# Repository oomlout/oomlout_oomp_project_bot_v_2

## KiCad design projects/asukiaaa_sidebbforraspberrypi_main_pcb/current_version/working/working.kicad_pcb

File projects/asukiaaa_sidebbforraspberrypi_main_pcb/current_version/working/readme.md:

# sidebbforraspberrypi
 
## summary 
* id: asukiaaa_sidebbforraspberrypi_main_pcb
* user: asukiaaa
* name: sidebbforraspberrypi
* board: main_pcb
* repo: https://github.com/asukiaaa/SideBBForRaspberryPi
* src_file_repo_kicad_pcb: main_pcb/main_pcb.kicad_pcb
* src_file_repo_kicad_pcb_link: https://github.com/asukiaaa/SideBBForRaspberryPi/tree/master/main_pcb/main_pcb.kicad_pcb

* src_file_repo_sch: main_pcb/main_pcb.sch
* src_file_repo_sch_link: https://github.com/asukiaaa/SideBBForRaspberryPi/tree/master/main_pcb/main_pcb.sch
* full details link: https://github.com/oomlout/oomlout_oomp_project_bot_v_2/tree/main/projects/asukiaaa_sidebbforraspberrypi_main_pcb/current_version/working  

## schematic  
  
[schematic (pdf)](working_schematic.pdf) 

## pcb  

[board (pdf)](working.pdf)  

## working_bom
| Id | Designator | Footprint | Quantity | Designation | Supplier and ref |  | None | 
| --- | --- | --- | --- | --- | --- | --- | --- | 
| 1 | P1 | PinHeader_2x20_P2.54mm_Vertical | 1 | Conn_02x20_Odd_Even |  |  | [''] | 
| 2 | J1,J2 | PinSocket_1x17_P2.54mm_Vertical | 2 | Conn_01x17 |  |  | [''] | 

## bom_schematic
| Ref | Qnty | Value | Cmp name | Footprint | Description | Vendor | DNP | 
| --- | --- | --- | --- | --- | --- | --- | --- | 
| J1, J2 | 2 | Conn_01x17 | Conn_01x17 | Connector_PinSocket_2.54mm:PinSocket_1x17_P2.54mm_Vertical | Generic connector, single row, 01x17, script generated (kicad-library-utils/schlib/autogen/connector/) |  |  | 
| MK1, MK2, MK3, MK4 | 4 | M2.5 | Mounting_Hole-Mechanical-main_pcb-rescue | MountingHole:MountingHole_2.7mm_M2.5 |  |  |  | 
| P1 | 1 | Conn_02x20_Odd_Even | Conn_02x20_Odd_Even | Connector_PinHeader_2.54mm:PinHeader_2x20_P2.54mm_Vertical | Generic connector, double row, 02x20, odd/even pin numbering scheme (row 1 odd numbers, row 2 even numbers), script generated (kicad-library-utils/schlib/autogen/connector/) |  |  |

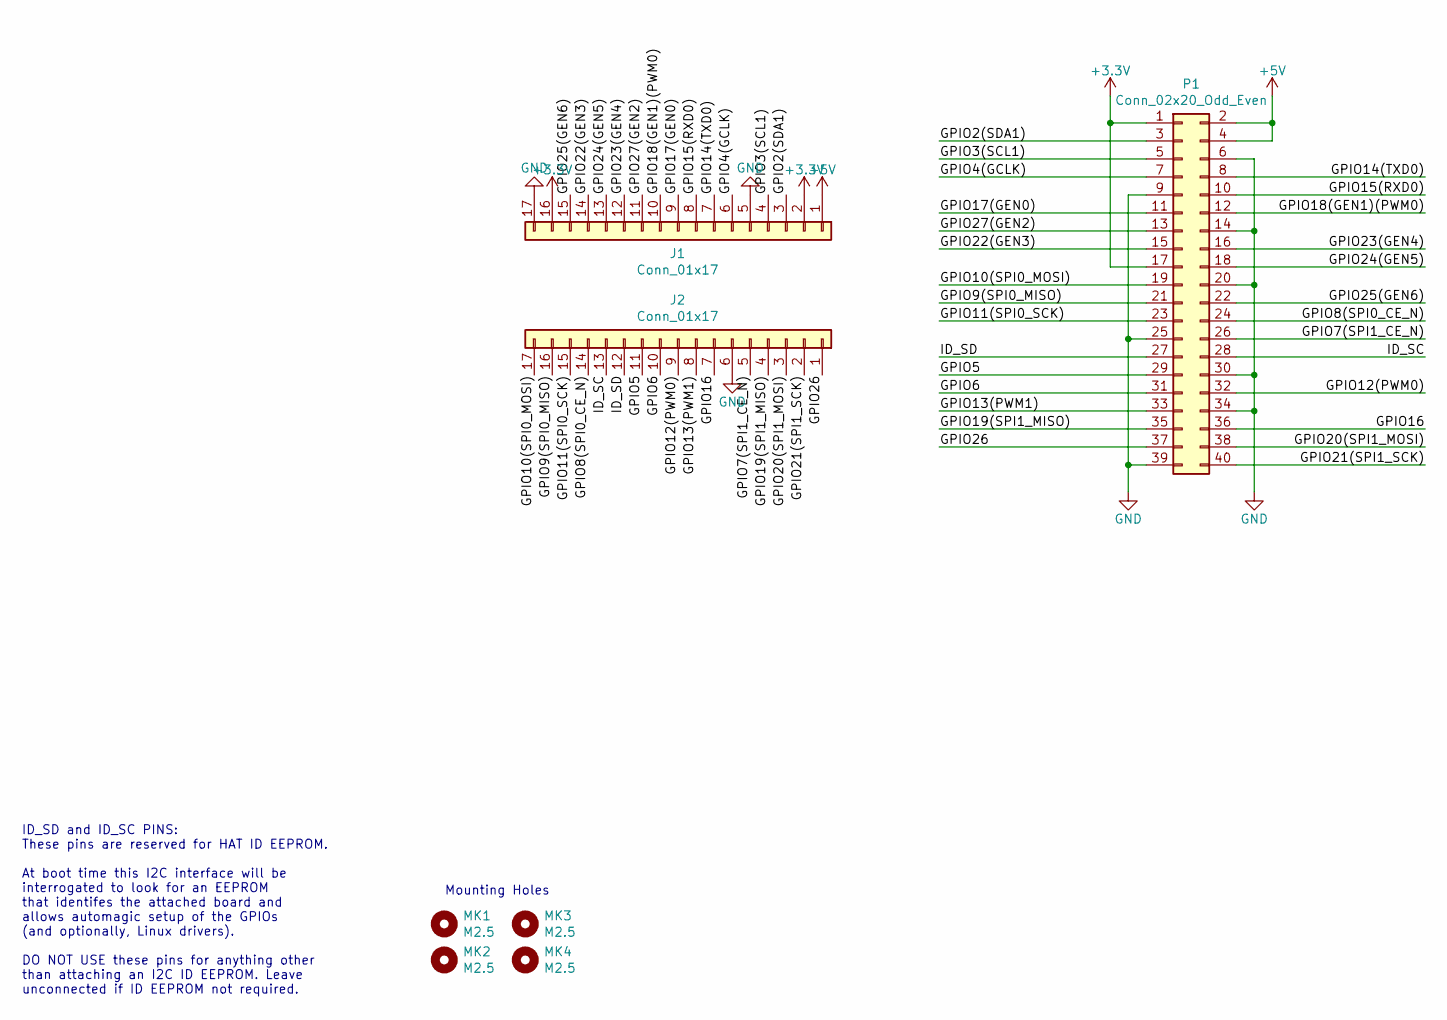
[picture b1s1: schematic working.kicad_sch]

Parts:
J1, J2: Conn_01x17; PinSocket_1x17_P2.54mm_Vertical
MK1, MK2, MK3, MK4: M2.5; MountingHole_2.7mm_M2.5
P1: Conn_02x20_Odd_Even; PinHeader_2x20_P2.54mm_Vertical

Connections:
+3V3: J1.2, J1.16, P1.1, P1.17
+5V: J1.1, P1.2, P1.4
/GPIO2(SDA1): J1.3, P1.3
/GPIO3(SCL1): J1.4, P1.5
/GPIO4(GCLK): J1.6, P1.7
/GPIO5: J2.11, P1.29
/GPIO6: J2.10, P1.31
/GPIO7(SPI1_CE_N): J2.5, P1.26
/GPIO8(SPI0_CE_N): J2.14, P1.24
/GPIO9(SPI0_MISO): J2.16, P1.21
/GPIO10(SPI0_MOSI): J2.17, P1.19
/GPIO11(SPI0_SCK): J2.15, P1.23
/GPIO12(PWM0): J2.9, P1.32
/GPIO13(PWM1): J2.8, P1.33
/GPIO14(TXD0): J1.7, P1.8
/GPIO15(RXD0): J1.8, P1.10
/GPIO16: J2.7, P1.36
/GPIO17(GEN0): J1.9, P1.11
/GPIO18(GEN1)(PWM0): J1.10, P1.12
/GPIO19(SPI1_MISO): J2.4, P1.35
/GPIO20(SPI1_MOSI): J2.3, P1.38
/GPIO21(SPI1_SCK): J2.2, P1.40
/GPIO22(GEN3): J1.14, P1.15
/GPIO23(GEN4): J1.12, P1.16
/GPIO24(GEN5): J1.13, P1.18
/GPIO25(GEN6): J1.15, P1.22
/GPIO26: J2.1, P1.37
/GPIO27(GEN2): J1.11, P1.13
/ID_SC: J2.13, P1.28
/ID_SD: J2.12, P1.27
GND: J1.5, J1.17, J2.6, P1.6, P1.9, P1.14, P1.20, P1.25, P1.30, P1.34, P1.39

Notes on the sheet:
Mounting Holes
ID_SD and ID_SC PINS: These pins are reserved for HAT ID EEPROM. At boot time this I2C interface will be interrogated to look for an EEPROM that identifes the attached board and allows automagic setup of the GPIOs (and optionally, Linux drivers). DO NOT USE these pins for anything other than attach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

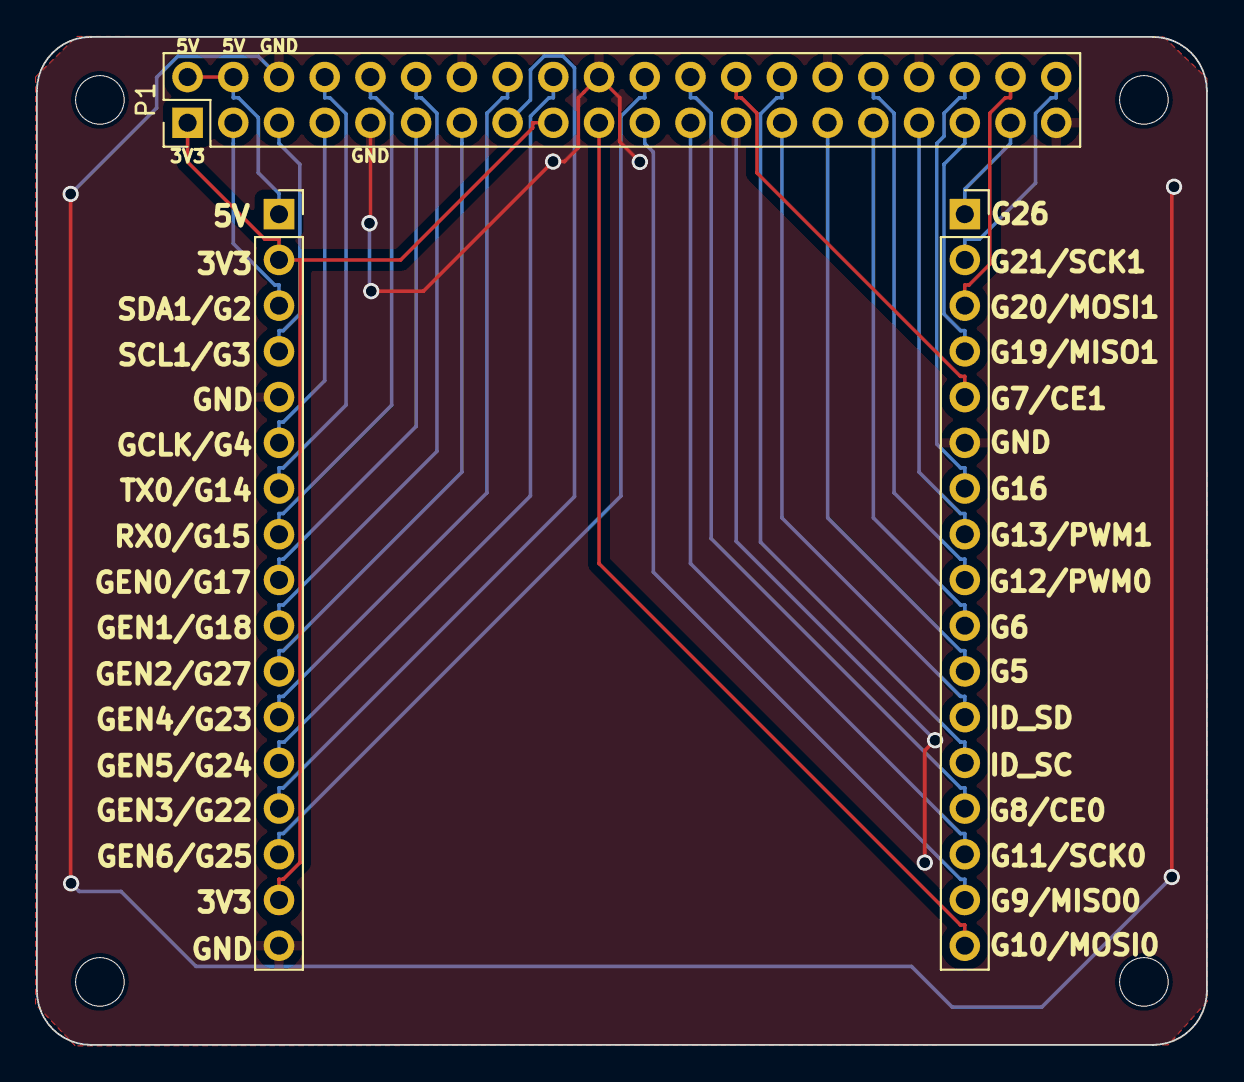
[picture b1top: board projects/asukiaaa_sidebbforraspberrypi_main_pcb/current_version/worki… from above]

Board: 2 copper layers, 65.0 x 56.0 mm, 7 parts (0 on the bottom side), 31 nets.

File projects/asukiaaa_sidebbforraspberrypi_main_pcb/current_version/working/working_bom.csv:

"Id";"Designator";"Footprint";"Quantity";"Designation";"Supplier and ref";
1;"P1";"PinHeader_2x20_P2.54mm_Vertical";1;"Conn_02x20_Odd_Even";;;
2;"J1,J2";"PinSocket_1x17_P2.54mm_Vertical";2;"Conn_01x17";;;

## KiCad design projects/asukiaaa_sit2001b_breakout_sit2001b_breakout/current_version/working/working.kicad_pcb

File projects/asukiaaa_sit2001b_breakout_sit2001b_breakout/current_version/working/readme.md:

# sit2001b_breakout
 
## summary 
* id: asukiaaa_sit2001b_breakout_sit2001b_breakout
* user: asukiaaa
* name: sit2001b_breakout
* board: sit2001b_breakout
* repo: https://github.com/asukiaaa/SIT2001B-breakout
* src_file_repo_kicad_pcb: SIT2001B-breakout.kicad_pcb
* src_file_repo_kicad_pcb_link: https://github.com/asukiaaa/SIT2001B-breakout/tree/master/SIT2001B-breakout.kicad_pcb

* src_file_repo_sch: SIT2001B-breakout.sch
* src_file_repo_sch_link: https://github.com/asukiaaa/SIT2001B-breakout/tree/master/SIT2001B-breakout.sch
* full details link: https://github.com/oomlout/oomlout_oomp_project_bot_v_2/tree/main/projects/asukiaaa_sit2001b_breakout_sit2001b_breakout/current_version/working  

## schematic  
  
[schematic (pdf)](working_schematic.pdf) 

## pcb  

[board (pdf)](working.pdf)  

## working_bom
| Id | Designator | Footprint | Quantity | Designation | Supplier and ref |  | None | 
| --- | --- | --- | --- | --- | --- | --- | --- | 
| 1 | C1 | C_0603_1608Metric | 1 | 15pf |  |  | [''] | 
| 2 | C2,C3 | C_0603_1608Metric | 2 | 0.1uf |  |  | [''] | 
| 3 | C4 | C_0603_1608Metric | 1 | 1uf |  |  | [''] | 
| 4 | J1 | Pin_1x03_P2.54mm_nosilk | 1 | Conn_01x03 |  |  | [''] | 
| 5 | R1 | R_0603_1608Metric | 1 | 10k |  |  | [''] | 
| 6 | U1 | SOT-23-5 | 1 | SiT2001B-MEMS-Clock-Generator |  |  | [''] | 
| 7 | U2 | SOT-23-5 | 1 | NJM2866F33 |  |  | [''] | 

## bom_schematic
| Ref | Qnty | Value | Cmp name | Footprint | Description | Vendor | DNP | 
| --- | --- | --- | --- | --- | --- | --- | --- | 
| C1 | 1 | 15pf | C | Capacitor_SMD:C_0603_1608Metric | Unpolarized capacitor |  |  | 
| C2, C3 | 2 | 0.1uf | C | Capacitor_SMD:C_0603_1608Metric | Unpolarized capacitor |  |  | 
| C4 | 1 | 1uf | C | Capacitor_SMD:C_0603_1608Metric | Unpolarized capacitor |  |  | 
| J1 | 1 | Conn_01x03 | Conn_01x03 | my-kicad-footprints:Pin_1x03_P2.54mm_nosilk | Generic connector, single row, 01x03, script generated (kicad-library-utils/schlib/autogen/connector/) |  |  | 
| R1 | 1 | 10k | R | Resistor_SMD:R_0603_1608Metric | Resistor |  |  | 
| U1 | 1 | SiT2001B-MEMS-Clock-Generator | SiT2001B-MEMS-Clock-Generator-my-kicad-symbols | Package_TO_SOT_SMD:SOT-23-5 |  |  |  | 
| U2 | 1 | NJM2866F33 | NJM2866F33-my-kicad-symbols | Package_TO_SOT_SMD:SOT-23-5 |  |  |  |

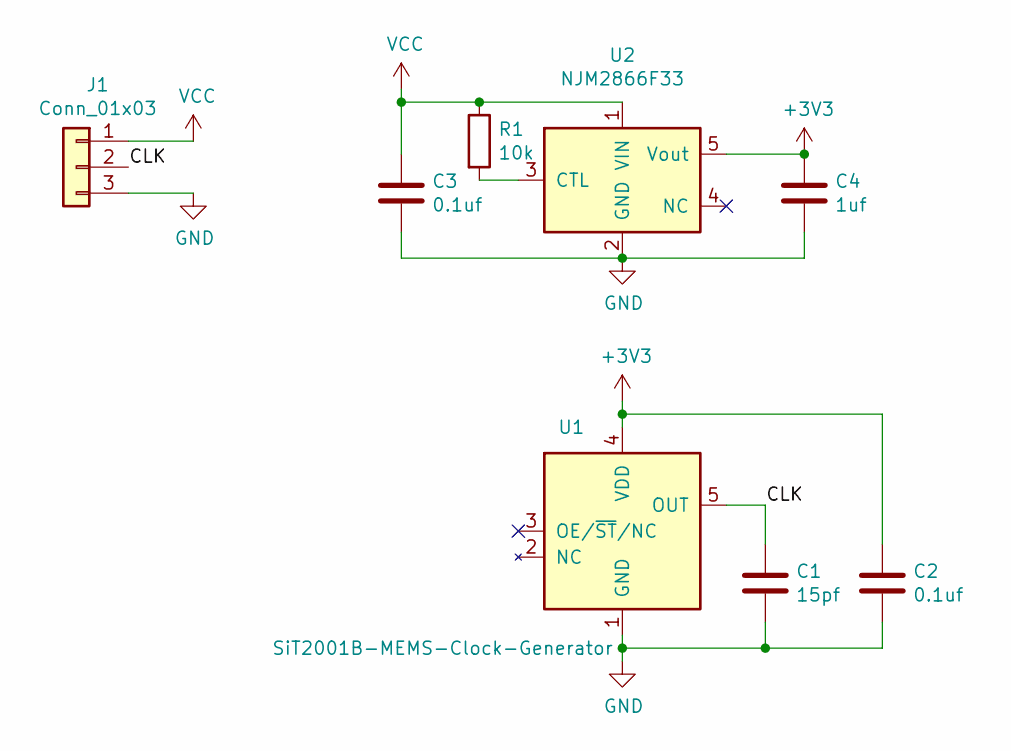
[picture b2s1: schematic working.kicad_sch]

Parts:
C1: 15pf; C_0603_1608Metric
C2, C3: 0.1uf; C_0603_1608Metric
C4: 1uf; C_0603_1608Metric
J1: Conn_01x03; Pin_1x03_P2.54mm_nosilk
R1: 10k; R_0603_1608Metric
U1: SiT2001B-MEMS-Clock-Generator; SOT-23-5
U2: NJM2866F33; SOT-23-5

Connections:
+3V3: C2.1, C4.1, U1.4 (VDD), U2.5 (Vout)
/CLK: C1.1, J1.2, U1.5 (OUT)
GND: C1.2, C2.2, C3.2, C4.2, J1.3, U1.1 (GND), U2.2 (GND)
unnamed: R1.2, U2.3 (CTL)
VCC: C3.1, J1.1, R1.1, U2.1 (VIN)

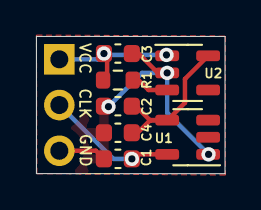
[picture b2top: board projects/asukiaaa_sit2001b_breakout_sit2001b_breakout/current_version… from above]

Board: 2 copper layers, 10.5 x 7.6 mm, 8 parts (0 on the bottom side), 5 nets.

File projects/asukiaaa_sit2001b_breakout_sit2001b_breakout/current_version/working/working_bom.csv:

"Id";"Designator";"Footprint";"Quantity";"Designation";"Supplier and ref";
1;"C1";"C_0603_1608Metric";1;"15pf";;;
2;"C2,C3";"C_0603_1608Metric";2;"0.1uf";;;
3;"C4";"C_0603_1608Metric";1;"1uf";;;
4;"J1";"Pin_1x03_P2.54mm_nosilk";1;"Conn_01x03";;;
5;"R1";"R_0603_1608Metric";1;"10k";;;
6;"U1";"SOT-23-5";1;"SiT2001B-MEMS-Clock-Generator";;;
7;"U2";"SOT-23-5";1;"NJM2866F33";;;

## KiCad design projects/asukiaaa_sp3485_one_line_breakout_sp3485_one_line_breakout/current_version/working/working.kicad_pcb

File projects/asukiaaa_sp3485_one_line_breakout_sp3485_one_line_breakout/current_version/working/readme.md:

# sp3485_one_line_breakout
 
## summary 
* id: asukiaaa_sp3485_one_line_breakout_sp3485_one_line_breakout
* user: asukiaaa
* name: sp3485_one_line_breakout
* board: sp3485_one_line_breakout
* repo: https://github.com/asukiaaa/sp3485-one-line-breakout
* src_file_repo_kicad_pcb: sp3485-one-line-breakout.kicad_pcb
* src_file_repo_kicad_pcb_link: https://github.com/asukiaaa/sp3485-one-line-breakout/tree/master/sp3485-one-line-breakout.kicad_pcb

* src_file_repo_sch: sp3485-one-line-breakout.sch
* src_file_repo_sch_link: https://github.com/asukiaaa/sp3485-one-line-breakout/tree/master/sp3485-one-line-breakout.sch
* full details link: https://github.com/oomlout/oomlout_oomp_project_bot_v_2/tree/main/projects/asukiaaa_sp3485_one_line_breakout_sp3485_one_line_breakout/current_version/working  

## schematic  
  
[schematic (pdf)](working_schematic.pdf) 

## pcb  

[board (pdf)](working.pdf)  

## working_bom
| Id | Designator | Footprint | Quantity | Designation | Supplier and ref |  | None | 
| --- | --- | --- | --- | --- | --- | --- | --- | 
| 1 | R1 | R_0402_1005Metric | 1 | 220 |  |  | [''] | 
| 2 | U1 | SOIC-8_3.9x4.9mm_P1.27mm | 1 | SP3485CN |  |  | [''] | 
| 3 | J1 | PinHeader_1x08_P2.54mm_Vertical_witout_silk | 1 | Conn_01x08 |  |  | [''] | 
| 4 | C1 | C_0402_1005Metric | 1 | 0.1uf |  |  | [''] | 

## bom_schematic
| Ref | Qnty | Value | Cmp name | Footprint | Description | Vendor | DNP | 
| --- | --- | --- | --- | --- | --- | --- | --- | 
| C1 | 1 | 0.1uf | C | Capacitor_SMD:C_0402_1005Metric | Unpolarized capacitor |  |  | 
| J1 | 1 | Conn_01x08 | Conn_01x08 | my-kicad-footprints:PinHeader_1x08_P2.54mm_Vertical_witout_silk | Generic connector, single row, 01x08, script generated (kicad-library-utils/schlib/autogen/connector/) |  |  | 
| JP1 | 1 | Bridged | SolderJumper_2_Bridged | my-kicad-footprints:SolderJumper-2_P1.3mm_Bridged_RoundedPad1.0x1.5mm | Solder Jumper, 2-pole, closed/bridged |  |  | 
| R1 | 1 | 220 | R | Resistor_SMD:R_0402_1005Metric | Resistor |  |  | 
| U1 | 1 | SP3485CN | SP3485CN | Package_SO:SOIC-8_3.9x4.9mm_P1.27mm | 3.3V Low Power Half-Duplex RS-485 Transceiver 10Mbps, SOIC-8 |  |  |

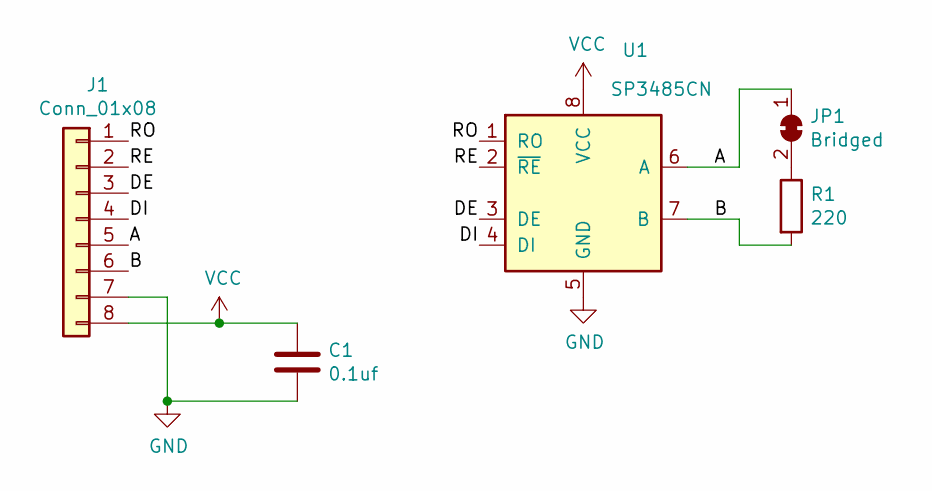
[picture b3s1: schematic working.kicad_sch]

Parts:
C1: 0.1uf; C_0402_1005Metric
J1: Conn_01x08; PinHeader_1x08_P2.54mm_Vertical_witout_silk
JP1: Bridged; SolderJumper-2_P1.3mm_Bridged_RoundedPad1.0x1.5mm
R1: 220; R_0402_1005Metric
U1: SP3485CN; SOIC-8_3.9x4.9mm_P1.27mm

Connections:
/A: J1.5, JP1.1 (A), U1.6 (A)
/B: J1.6, R1.2, U1.7 (B)
/DE: J1.3, U1.3 (DE)
/DI: J1.4, U1.4 (DI)
/RE: J1.2, U1.2 (~RE)
/RO: J1.1, U1.1 (RO)
GND: C1.2, J1.7, U1.5 (GND)
unnamed: JP1.2 (B), R1.1
VCC: C1.1, J1.8, U1.8 (VCC)

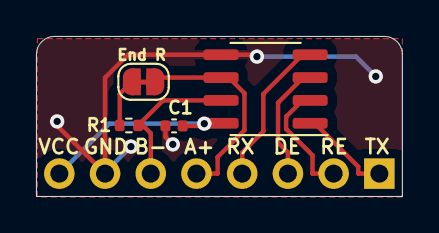
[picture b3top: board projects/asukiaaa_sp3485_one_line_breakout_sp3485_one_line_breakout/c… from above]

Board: 2 copper layers, 20.3 x 8.9 mm, 5 parts (0 on the bottom side), 9 nets.

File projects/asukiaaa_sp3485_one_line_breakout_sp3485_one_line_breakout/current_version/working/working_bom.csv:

"Id";"Designator";"Footprint";"Quantity";"Designation";"Supplier and ref";
1;"R1";"R_0402_1005Metric";1;"220";;;
2;"U1";"SOIC-8_3.9x4.9mm_P1.27mm";1;"SP3485CN";;;
3;"J1";"PinHeader_1x08_P2.54mm_Vertical_witout_silk";1;"Conn_01x08";;;
4;"C1";"C_0402_1005Metric";1;"0.1uf";;;

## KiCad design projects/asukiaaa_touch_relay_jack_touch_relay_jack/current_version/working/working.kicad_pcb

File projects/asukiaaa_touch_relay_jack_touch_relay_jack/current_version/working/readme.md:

# touch_relay_jack
 
## summary 
* id: asukiaaa_touch_relay_jack_touch_relay_jack
* user: asukiaaa
* name: touch_relay_jack
* board: touch_relay_jack
* repo: https://github.com/asukiaaa/touch_relay_jack
* src_file_repo_kicad_pcb: pcb/touch_relay_jack.kicad_pcb
* src_file_repo_kicad_pcb_link: https://github.com/asukiaaa/touch_relay_jack/tree/master/pcb/touch_relay_jack.kicad_pcb

* src_file_repo_sch: pcb/touch_relay_jack.sch
* src_file_repo_sch_link: https://github.com/asukiaaa/touch_relay_jack/tree/master/pcb/touch_relay_jack.sch
* full details link: https://github.com/oomlout/oomlout_oomp_project_bot_v_2/tree/main/projects/asukiaaa_touch_relay_jack_touch_relay_jack/current_version/working  

## schematic  
  
[schematic (pdf)](working_schematic.pdf) 

## pcb  

[board (pdf)](working.pdf)  

## working_bom
| Id | Designator | Footprint | Quantity | Designation | Supplier and ref |  | None | 
| --- | --- | --- | --- | --- | --- | --- | --- | 
| 1 | A1 | Pro_Micro | 1 | Pro_Micro |  |  | [''] | 
| 2 | D1 | D_SOD-523 | 1 | D_Shockley |  |  | [''] | 
| 3 | D2 | LED_0603_1608Metric | 1 | LED |  |  | [''] | 
| 4 | J1 | Jack_3.5mm_Switronic_ST-005-G_horizontal | 1 | AudioJack3_Ground |  |  | [''] | 
| 5 | K1 | Relay_SPDT_HsinDa_Y14 | 1 | Y14x-1C-xxDS |  |  | [''] | 
| 6 | Q1 | SOT-23 | 1 | Q_NMOS_GSD |  |  | [''] | 
| 7 | R1,R2 | R_0603_1608Metric | 2 | 1K |  |  | [''] | 
| 8 | R3 | R_0603_1608Metric | 1 | 1M |  |  | [''] | 

## bom_schematic
no data

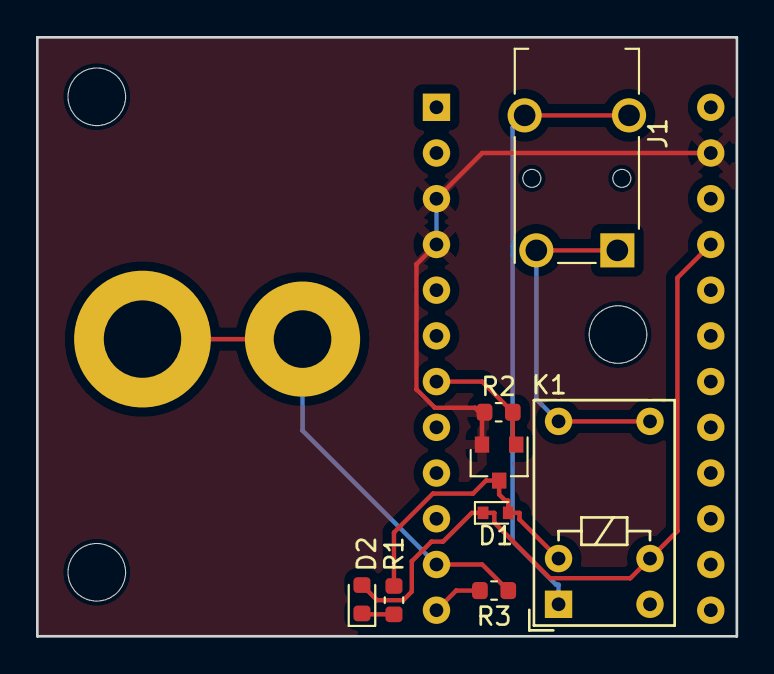
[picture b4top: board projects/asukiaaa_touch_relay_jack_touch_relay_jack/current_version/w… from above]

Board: 2 copper layers, 38.9 x 33.3 mm, 14 parts (0 on the bottom side), 9 nets.

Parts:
A1: Pro_Micro
D1: D_Shockley; D_SOD-523
D2: LED; LED_0603_1608Metric
H1: M4Hole; MountingHole_4.3mm_M4_ISO7380_Pad
H2: M3Hole; MountingHole_3.2mm_M3_Pad
J1: AudioJack3_Ground; Jack_3.5mm_Switronic_ST-005-G_horizontal
K1: Y14x-1C-xxDS; Relay_SPDT_HsinDa_Y14
Q1: Q_NMOS_GSD; SOT-23
R1, R2: 1K; R_0603_1608Metric
R3: 1M; R_0603_1608Metric
REF1, REF2, REF3: MountingHole_3.2mm_M3

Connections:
+5V: A1.21, D1.1, D2.2, K1.4
GND: A1.3, A1.4, A1.23, Q1.2, R2.1
unnamed: A1.11, H1.1, H2.1, R3.1
unnamed: A1.12, R3.2
unnamed: D1.2, K1.3, Q1.3, R1.1
unnamed: D2.1, R1.2
unnamed: J1.R, J1.S, K1.5, K1.6
unnamed: J1.T, K1.1
Relay: A1.7, Q1.1, R2.2

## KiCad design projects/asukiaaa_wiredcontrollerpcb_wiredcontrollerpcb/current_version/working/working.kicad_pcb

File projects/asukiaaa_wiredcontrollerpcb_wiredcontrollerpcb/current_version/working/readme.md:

# wiredcontrollerpcb
 
## summary 
* id: asukiaaa_wiredcontrollerpcb_wiredcontrollerpcb
* user: asukiaaa
* name: wiredcontrollerpcb
* board: wiredcontrollerpcb
* repo: https://github.com/asukiaaa/WiredControllerPcb
* src_file_repo_kicad_pcb: WiredControllerPcb.kicad_pcb
* src_file_repo_kicad_pcb_link: https://github.com/asukiaaa/WiredControllerPcb/tree/master/WiredControllerPcb.kicad_pcb
* src_file_repo_kicad_sch: WiredControllerPcb.kicad_sch
* src_file_repo_kicad_sch_link: https://github.com/asukiaaa/WiredControllerPcb/tree/master/WiredControllerPcb.kicad_sch

* src_file_repo_sch: 
* src_file_repo_sch_link: https://github.com/asukiaaa/WiredControllerPcb/tree/master/
* full details link: https://github.com/oomlout/oomlout_oomp_project_bot_v_2/tree/main/projects/asukiaaa_wiredcontrollerpcb_wiredcontrollerpcb/current_version/working  

## schematic  
  
[schematic (pdf)](working_schematic.pdf) 

## pcb  

[board (pdf)](working.pdf)  

## working_bom
| Id | Designator | Footprint | Quantity | Designation | Supplier and ref |  | None | 
| --- | --- | --- | --- | --- | --- | --- | --- | 
| 1 | C1 | C_0603_1608Metric | 1 | 1u |  |  | [''] | 
| 2 | C2 | C_0603_1608Metric | 1 | 10n |  |  | [''] | 
| 3 | C3 | C_0603_1608Metric | 1 | 2.2u |  |  | [''] | 
| 4 | C4,C7,C8,C9,C10 | C_0603_1608Metric | 5 | 0.1u |  |  | [''] | 
| 5 | D1,D2,D3,D4 | LED_0603_1608Metric | 4 | LED |  |  | [''] | 
| 6 | J1 | PS4tJoystick | 1 | Joystick |  |  | [''] | 
| 7 | J3 | NS-Tech_Grove_1x04_P2mm_Horizontal | 1 | Conn_01x04 |  |  | [''] | 
| 8 | R1,R2,R3,R5,R6,R4 | R_0603_1608Metric | 6 | 1k |  |  | [''] | 
| 9 | SW1,SW2,SW3,SW4 | SW_Center_PUSH-12mm | 4 | SW_Push |  |  | [''] | 
| 10 | U1 | SOT-23-5 | 1 | LP2985-3.3 |  |  | [''] | 
| 11 | U2 | QFN-32-1EP_5x5mm_P0.5mm_EP3.1x3.1mm | 1 | ATmega328P-MU |  |  | [''] | 
| 12 | JP1,JP2,JP3 | SolderJumper-2_P1.3mm_Open_RoundedPad1.0x1.5mm | 3 | Jumper_NO |  |  | [''] | 
| 13 | J4 | TerminalBlock_bornier-4_P5.08mm | 1 | Conn_01x04 |  |  | [''] | 
| 14 | R7,R8,R9 | R_0603_1608Metric | 3 | 10k |  |  | [''] | 
| 15 | J5 | PinHeader_1x04_P2.54mm_Vertical | 1 | Conn_01x04 |  |  | [''] | 
| 16 | J2 | 2x03_P2.54mm_Pads | 1 | Conn_01x06 |  |  | [''] | 

## bom_schematic
| Ref | Qnty | Value | Cmp name | Footprint | Description | Vendor | DNP | 
| --- | --- | --- | --- | --- | --- | --- | --- | 
| C1 | 1 | 1u | C | Capacitor_SMD:C_0603_1608Metric | Unpolarized capacitor |  |  | 
| C2 | 1 | 10n | C | Capacitor_SMD:C_0603_1608Metric | Unpolarized capacitor |  |  | 
| C3 | 1 | 2.2u | C | Capacitor_SMD:C_0603_1608Metric | Unpolarized capacitor |  |  | 
| C4, C7, C8, C9, C10 | 5 | 0.1u | C | Capacitor_SMD:C_0603_1608Metric | Unpolarized capacitor |  |  | 
| D1, D2, D3, D4 | 4 | LED | LED | LED_SMD:LED_0603_1608Metric | Light emitting diode |  |  | 
| J1 | 1 | Joystick | Conn_01x08 | footprints:PS4tJoystick | Generic connector, single row, 01x08, script generated (kicad-library-utils/schlib/autogen/connector/) |  |  | 
| J2 | 1 | Conn_01x06 | Conn_01x06 | footprints:2x03_P2.54mm_Pads | Generic connector, single row, 01x06, script generated (kicad-library-utils/schlib/autogen/connector/) |  |  | 
| J3 | 1 | Conn_01x04 | Conn_01x04 | footprints:NS-Tech_Grove_1x04_P2mm_Horizontal | Generic connector, single row, 01x04, script generated (kicad-library-utils/schlib/autogen/connector/) |  |  | 
| J4 | 1 | Conn_01x04 | Conn_01x04 | TerminalBlock:TerminalBlock_bornier-4_P5.08mm | Generic connector, single row, 01x04, script generated (kicad-library-utils/schlib/autogen/connector/) |  |  | 
| J5 | 1 | Conn_01x04 | Conn_01x04 | Connector_PinHeader_2.54mm:PinHeader_1x04_P2.54mm_Vertical | Generic connector, single row, 01x04, script generated (kicad-library-utils/schlib/autogen/connector/) |  |  | 
| JP1, JP2, JP3 | 3 | Jumper_NO | Jumper_2_Open | Jumper:SolderJumper-2_P1.3mm_Open_RoundedPad1.0x1.5mm | Jumper, 2-pole, open |  |  | 
| R1, R2, R3, R4, R5, R6 | 6 | 1k | R | Resistor_SMD:R_0603_1608Metric | Resistor |  |  | 
| R7, R8, R9 | 3 | 10k | R | Resistor_SMD:R_0603_1608Metric | Resistor |  |  | 
| SW1, SW2, SW3, SW4 | 4 | SW_Push | SW_Push | footprints:SW_Center_PUSH-12mm | Push button switch, generic, two pins |  |  | 
| U1 | 1 | LP2985-3.3 | LP2985-3.3 | Package_TO_SOT_SMD:SOT-23-5 | 150mA 16V Low-noise Low-dropout Regulator With Shutdown, 3.3V output voltage, SOT-23-5 |  |  | 
| U2 | 1 | ATmega328P-MU | ATmega328P-MU-MCU_Microchip_ATmega | Package_DFN_QFN:QFN-32-1EP_5x5mm_P0.5mm_EP3.1x3.1mm |  |  |  |

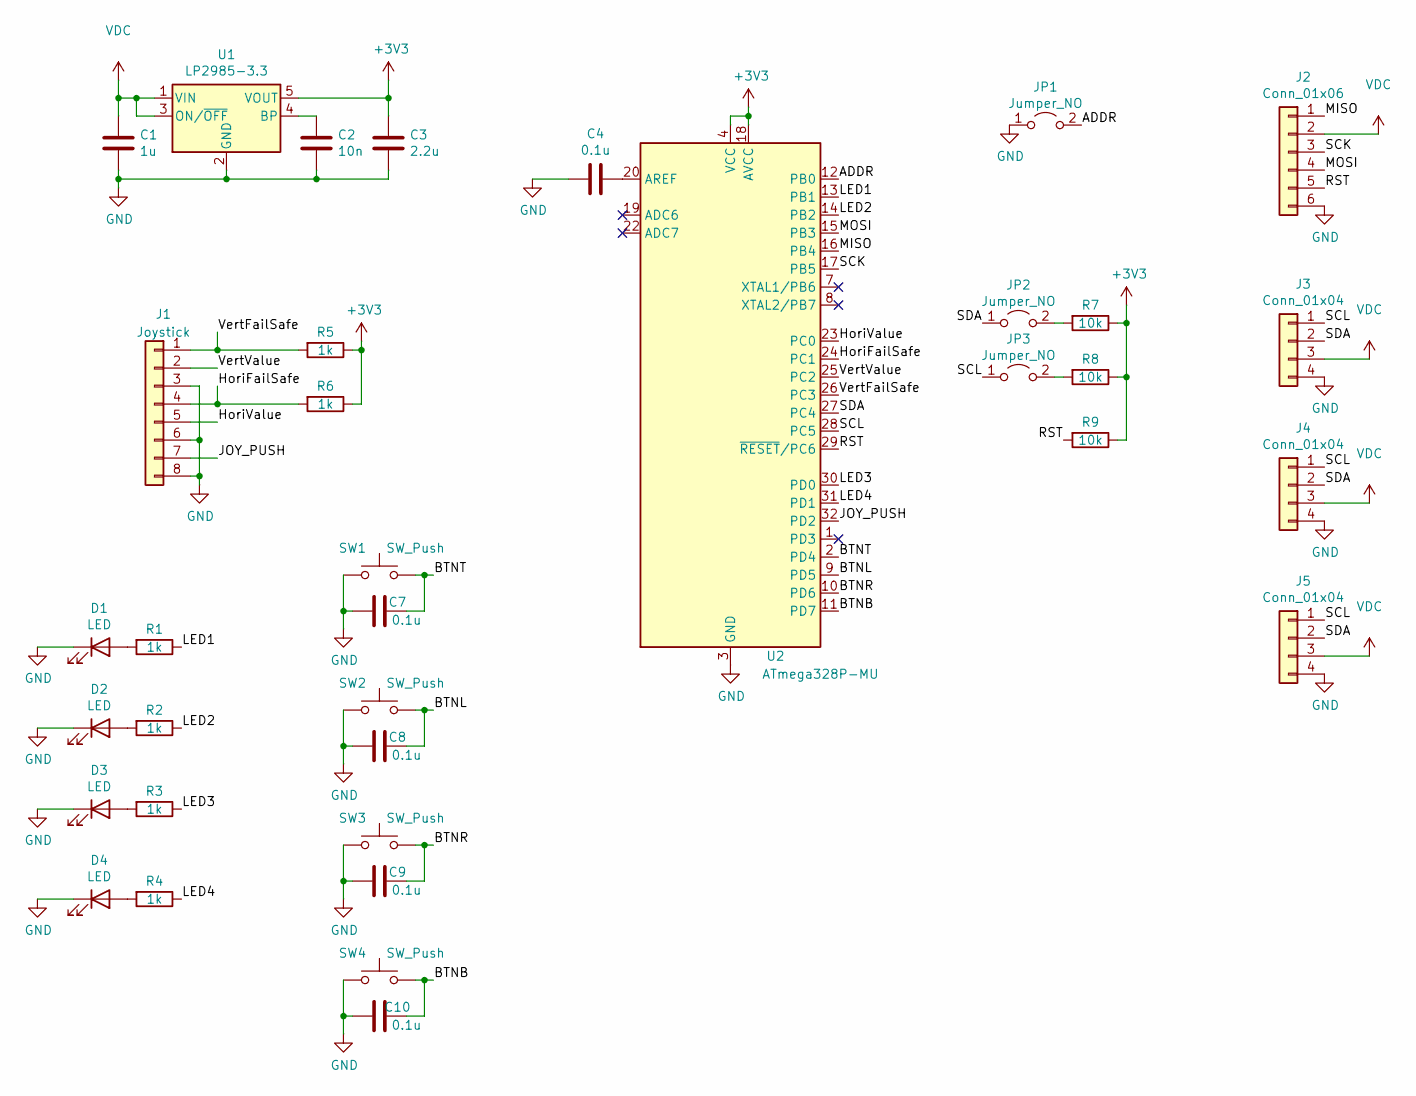
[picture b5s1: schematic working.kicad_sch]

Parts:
C1: 1u; C_0603_1608Metric
C2: 10n; C_0603_1608Metric
C3: 2.2u; C_0603_1608Metric
C4, C7, C8, C9, C10: 0.1u; C_0603_1608Metric
D1, D2, D3, D4: LED; LED_0603_1608Metric
J1: Joystick; PS4tJoystick
J2: Conn_01x06; 2x03_P2.54mm_Pads
J3: Conn_01x04; NS-Tech_Grove_1x04_P2mm_Horizontal
J4: Conn_01x04; TerminalBlock_bornier-4_P5.08mm
J5: Conn_01x04; PinHeader_1x04_P2.54mm_Vertical
JP1, JP2, JP3: Jumper_NO; SolderJumper-2_P1.3mm_Open_RoundedPad1.0x1.5mm
R1, R2, R3, R4, R5, R6: 1k; R_0603_1608Metric
R7, R8, R9: 10k; R_0603_1608Metric
SW1, SW2, SW3, SW4: SW_Push; SW_Center_PUSH-12mm
U1: LP2985-3.3; SOT-23-5
U2: ATmega328P-MU; QFN-32-1EP_5x5mm_P0.5mm_EP3.1x3.1mm

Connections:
+3V3: C3.1, R5.1, R6.1, R7.1, R8.1, R9.1, U1.5 (VOUT), U2.4 (VCC), U2.6 (VCC), U2.18 (AVCC)
/ADDR: JP1.2 (B), U2.12 (PB0)
/BTNB: C10.1, SW4.2, U2.11 (PD7)
/BTNL: C8.1, SW2.2, U2.9 (PD5)
/BTNR: C9.1, SW3.2, U2.10 (PD6)
/BTNT: C7.1, SW1.2, U2.2 (PD4)
/HoriFailSafe: J1.4, R6.2, U2.24 (PC1)
/HoriValue: J1.5, U2.23 (PC0)
/JOY_PUSH: J1.7, U2.32 (PD2)
/LED1: R1.1, U2.13 (PB1)
/LED2: R2.1, U2.14 (PB2)
/LED3: R3.1, U2.30 (PD0)
/LED4: R4.1, U2.31 (PD1)
/MISO: J2.1, U2.16 (PB4)
/MOSI: J2.4, U2.15 (PB3)
/RST: J2.5, R9.2, U2.29 (~RESET/PC6)
/SCK: J2.3, U2.17 (PB5)
/SCL: J3.1, J4.1, J5.1, JP3.1 (A), U2.28 (PC5)
/SDA: J3.2, J4.2, J5.2, JP2.1 (A), U2.27 (PC4)
/VertFailSafe: J1.1, R5.2, U2.26 (PC3)
/VertValue: J1.2, U2.25 (PC2)
GND: C1.2, C2.2, C3.2, C4.1, C7.2, C8.2, C9.2, C10.2, D1.1 (K), D2.1 (K), D3.1 (K), D4.1 (K), J1.3, J1.6, J1.8, J2.6, J3.4, J4.4, J5.4, JP1.1 (A), SW1.1, SW2.1, SW3.1, SW4.1, U1.2 (GND), U2.3 (GND), U2.5 (GND), U2.21 (GND), U2.33 (GND)
unnamed: C2.1, U1.4 (BP)
unnamed: C4.2, U2.20 (AREF)
unnamed: D1.2 (A), R1.2
unnamed: D2.2 (A), R2.2
unnamed: D3.2 (A), R3.2
unnamed: D4.2 (A), R4.2
unnamed: JP2.2 (B), R7.2
unnamed: JP3.2 (B), R8.2
VDC: C1.1, J2.2, J3.3, J4.3, J5.3, U1.1 (VIN), U1.3 (ON/~OFF)

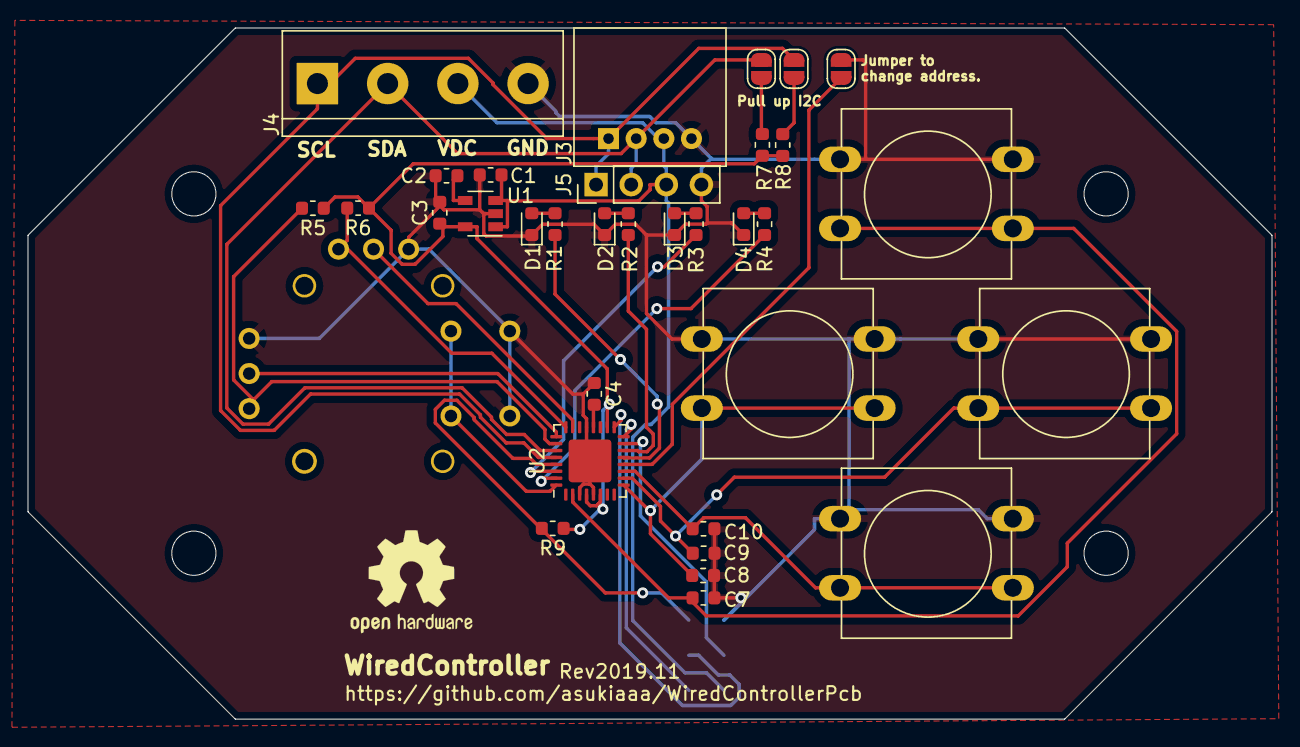
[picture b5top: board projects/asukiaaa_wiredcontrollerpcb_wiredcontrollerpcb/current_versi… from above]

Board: 2 copper layers, 90.0 x 50.0 mm, 39 parts (1 on the bottom side), 31 nets.

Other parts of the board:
REF1, REF2, REF3, REF4: MountingHole_3.2mm_M3

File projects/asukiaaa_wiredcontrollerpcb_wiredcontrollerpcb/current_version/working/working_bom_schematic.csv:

"Source:","C:\gh\oomlout_oomp_project_bot_v_2\projects\asukiaaa_wiredcontrollerpcb_wiredcontrollerpcb\current_version\working\working.kicad_sch"
"Date:","25/09/2023 23:24:11"
"Tool:","Eeschema 7.0.6"
"Generator:","C:/Program Files/KiCad/7.0/bin/scripting/plugins/bom_csv_grouped_by_value_with_fp.py"
"Component Count:","35"
"Ref","Qnty","Value","Cmp name","Footprint","Description","Vendor","DNP"
"C1","1","1u","C","Capacitor_SMD:C_0603_1608Metric","Unpolarized capacitor","",""
"C2","1","10n","C","Capacitor_SMD:C_0603_1608Metric","Unpolarized capacitor","",""
"C3","1","2.2u","C","Capacitor_SMD:C_0603_1608Metric","Unpolarized capacitor","",""
"C4, C7, C8, C9, C10","5","0.1u","C","Capacitor_SMD:C_0603_1608Metric","Unpolarized capacitor","",""
"D1, D2, D3, D4","4","LED","LED","LED_SMD:LED_0603_1608Metric","Light emitting diode","",""
"J1","1","Joystick","Conn_01x08","footprints:PS4tJoystick","Generic connector, single row, 01x08, script generated (kicad-library-utils/schlib/autogen/connector/)","",""
"J2","1","Conn_01x06","Conn_01x06","footprints:2x03_P2.54mm_Pads","Generic connector, single row, 01x06, script generated (kicad-library-utils/schlib/autogen/connector/)","",""
"J3","1","Conn_01x04","Conn_01x04","footprints:NS-Tech_Grove_1x04_P2mm_Horizontal","Generic connector, single row, 01x04, script generated (kicad-library-utils/schlib/autogen/connector/)","",""
"J4","1","Conn_01x04","Conn_01x04","TerminalBlock:TerminalBlock_bornier-4_P5.08mm","Generic connector, single row, 01x04, script generated (kicad-library-utils/schlib/autogen/connector/)","",""
"J5","1","Conn_01x04","Conn_01x04","Connector_PinHeader_2.54mm:PinHeader_1x04_P2.54mm_Vertical","Generic connector, single row, 01x04, script generated (kicad-library-utils/schlib/autogen/connector/)","",""
"JP1, JP2, JP3","3","Jumper_NO","Jumper_2_Open","Jumper:SolderJumper-2_P1.3mm_Open_RoundedPad1.0x1.5mm","Jumper, 2-pole, open","",""
"R1, R2, R3, R4, R5, R6","6","1k","R","Resistor_SMD:R_0603_1608Metric","Resistor","",""
"R7, R8, R9","3","10k","R","Resistor_SMD:R_0603_1608Metric","Resistor","",""
"SW1, SW2, SW3, SW4","4","SW_Push","SW_Push","footprints:SW_Center_PUSH-12mm","Push button switch, generic, two pins","",""
"U1","1","LP2985-3.3","LP2985-3.3","Package_TO_SOT_SMD:SOT-23-5","150mA 16V Low-noise Low-dropout Regulator With Shutdown, 3.3V output voltage, SOT-23-5","",""
"U2","1","ATmega328P-MU","ATmega328P-MU-MCU_Microchip_ATmega","Package_DFN_QFN:QFN-32-1EP_5x5mm_P0.5mm_EP3.1x3.1mm","","",""

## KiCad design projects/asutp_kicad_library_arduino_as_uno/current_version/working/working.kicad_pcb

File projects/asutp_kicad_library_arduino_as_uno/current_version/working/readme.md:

# kicad_library
 
## summary 
* id: asutp_kicad_library_arduino_as_uno
* user: asutp
* name: kicad_library
* board: arduino_as_uno
* repo: https://github.com/asutp/kicad-library
* src_file_repo_kicad_pcb: template/Arduino_As_Uno_R3/Arduino_As_Uno.kicad_pcb
* src_file_repo_kicad_pcb_link: https://github.com/asutp/kicad-library/tree/master/template/Arduino_As_Uno_R3/Arduino_As_Uno.kicad_pcb

* src_file_repo_sch: template/Arduino_As_Uno_R3/Arduino_As_Uno.sch
* src_file_repo_sch_link: https://github.com/asutp/kicad-library/tree/master/template/Arduino_As_Uno_R3/Arduino_As_Uno.sch
* full details link: https://github.com/oomlout/oomlout_oomp_project_bot_v_2/tree/main/projects/asutp_kicad_library_arduino_as_uno/current_version/working  

## schematic  
  
[schematic (pdf)](working_schematic.pdf) 

## pcb  

[board (pdf)](working.pdf)  

## working_bom
| Id | Designator | Footprint | Quantity | Designation | Supplier and ref |  | None | 
| --- | --- | --- | --- | --- | --- | --- | --- | 
| 1 | P1 | Socket_Strip_Arduino_1x08 | 1 | Power |  |  | [''] | 
| 2 | P2 | Socket_Strip_Arduino_1x06 | 1 | Analog |  |  | [''] | 
| 3 | P3 | Socket_Strip_Arduino_1x10 | 1 | Digital |  |  | [''] | 
| 4 | P4 | Socket_Strip_Arduino_1x08 | 1 | Digital |  |  | [''] | 
| 5 | P5,P6,P7,P8 | Arduino_1pin | 4 | CONN_01X01 |  |  | [''] | 

## bom_schematic
| Ref | Qnty | Value | Cmp name | Footprint | Description | Vendor | DNP | 
| --- | --- | --- | --- | --- | --- | --- | --- | 
| P1 | 1 | Power | CONN_01X08 | Socket_Arduino_Uno:Socket_Strip_Arduino_1x08 |  |  |  | 
| P2 | 1 | Analog | CONN_01X06 | Socket_Arduino_Uno:Socket_Strip_Arduino_1x06 |  |  |  | 
| P3 | 1 | Digital | CONN_01X10 | Socket_Arduino_Uno:Socket_Strip_Arduino_1x10 |  |  |  | 
| P4 | 1 | Digital | CONN_01X08 | Socket_Arduino_Uno:Socket_Strip_Arduino_1x08 |  |  |  | 
| P5, P6, P7, P8 | 4 | CONN_01X01 | CONN_01X01 | Socket_Arduino_Uno:Arduino_1pin |  |  |  |

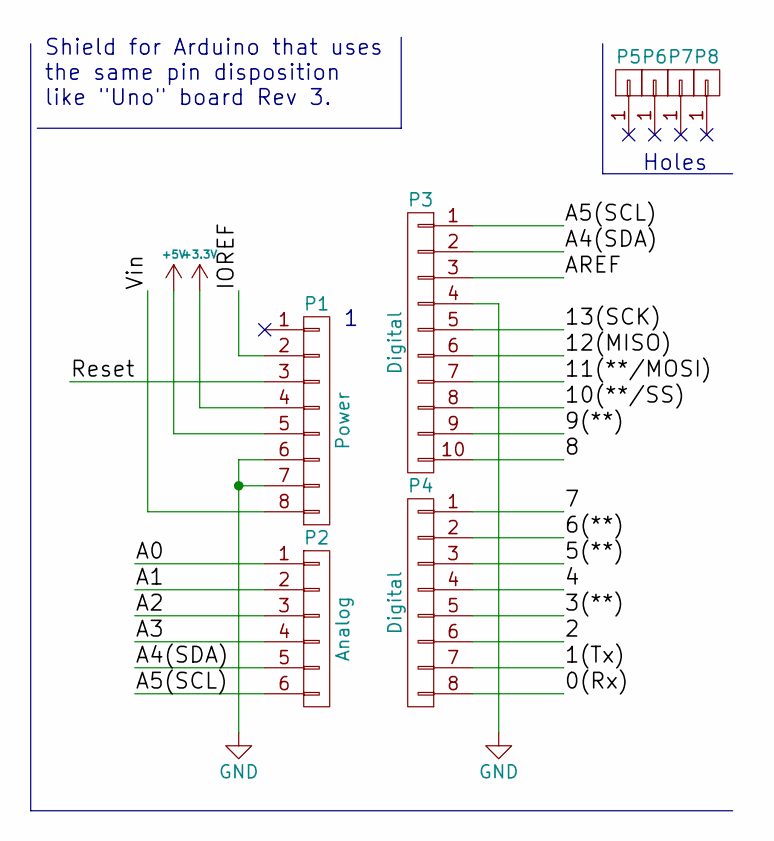
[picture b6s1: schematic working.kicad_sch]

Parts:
P1: Power; Socket_Strip_Arduino_1x08
P2: Analog; Socket_Strip_Arduino_1x06
P3: Digital; Socket_Strip_Arduino_1x10
P4: Digital; Socket_Strip_Arduino_1x08
P5, P6, P7, P8: CONN_01X01; Arduino_1pin

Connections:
+3V3: P1.4
+5V: P1.5
/0(Rx): P4.8
/1(Tx): P4.7
/2: P4.6
/3(**): P4.5
/4: P4.4
/5(**): P4.3
/6(**): P4.2
/7: P4.1
/8: P3.10
/9(**): P3.9
/10(**/SS): P3.8
/11(**/MOSI): P3.7
/12(MISO): P3.6
/13(SCK): P3.5
/A0: P2.1
/A1: P2.2
/A2: P2.3
/A3: P2.4
/A4(SDA): P2.5, P3.2
/A5(SCL): P2.6, P3.1
/AREF: P3.3
/IOREF: P1.2
/Reset: P1.3
/Vin: P1.8
GND: P1.6, P1.7, P3.4

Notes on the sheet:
Shield for Arduino that uses the same pin disposition like "Uno" board Rev 3.
Holes

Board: 2 copper layers, 8 parts (0 on the bottom side), 3 nets, no tracks yet.

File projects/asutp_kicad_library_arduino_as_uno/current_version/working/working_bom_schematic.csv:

"Source:","C:\gh\oomlout_oomp_project_bot_v_2\projects\asutp_kicad_library_arduino_as_uno\current_version\working\working.kicad_sch"
"Date:","25/09/2023 23:32:06"
"Tool:","Eeschema 7.0.6"
"Generator:","C:/Program Files/KiCad/7.0/bin/scripting/plugins/bom_csv_grouped_by_value_with_fp.py"
"Component Count:","8"
"Ref","Qnty","Value","Cmp name","Footprint","Description","Vendor","DNP"
"P1","1","Power","CONN_01X08","Socket_Arduino_Uno:Socket_Strip_Arduino_1x08","","",""
"P2","1","Analog","CONN_01X06","Socket_Arduino_Uno:Socket_Strip_Arduino_1x06","","",""
"P3","1","Digital","CONN_01X10","Socket_Arduino_Uno:Socket_Strip_Arduino_1x10","","",""
"P4","1","Digital","CONN_01X08","Socket_Arduino_Uno:Socket_Strip_Arduino_1x08","","",""
"P5, P6, P7, P8","4","CONN_01X01","CONN_01X01","Socket_Arduino_Uno:Arduino_1pin","","",""

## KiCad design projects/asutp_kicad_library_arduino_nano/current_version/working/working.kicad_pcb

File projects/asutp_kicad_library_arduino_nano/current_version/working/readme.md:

# kicad_library
 
## summary 
* id: asutp_kicad_library_arduino_nano
* user: asutp
* name: kicad_library
* board: arduino_nano
* repo: https://github.com/asutp/kicad-library
* src_file_repo_kicad_pcb: template/Arduino_Nano/Arduino_Nano.kicad_pcb
* src_file_repo_kicad_pcb_link: https://github.com/asutp/kicad-library/tree/master/template/Arduino_Nano/Arduino_Nano.kicad_pcb

* src_file_repo_sch: template/Arduino_Nano/Arduino_Nano.sch
* src_file_repo_sch_link: https://github.com/asutp/kicad-library/tree/master/template/Arduino_Nano/Arduino_Nano.sch
* full details link: https://github.com/oomlout/oomlout_oomp_project_bot_v_2/tree/main/projects/asutp_kicad_library_arduino_nano/current_version/working  

## schematic  
  
[schematic (pdf)](working_schematic.pdf) 

## pcb  

[board (pdf)](working.pdf)  

## working_bom
| Id | Designator | Footprint | Quantity | Designation | Supplier and ref |  | None | 
| --- | --- | --- | --- | --- | --- | --- | --- | 
| 1 | P1 | Socket_Strip_Arduino_1x15 | 1 | Digital |  |  | [''] | 
| 2 | P2 | Socket_Strip_Arduino_1x15 | 1 | Analog |  |  | [''] | 
| 3 | P3,P4,P5,P6 | 1pin_Nano | 4 | CONN_01X01 |  |  | [''] | 

## bom_schematic
| Ref | Qnty | Value | Cmp name | Footprint | Description | Vendor | DNP | 
| --- | --- | --- | --- | --- | --- | --- | --- | 
| P1 | 1 | Digital | CONN_01X15 | Socket_Arduino_Nano:Socket_Strip_Arduino_1x15 |  |  |  | 
| P2 | 1 | Analog | CONN_01X15 | Socket_Arduino_Nano:Socket_Strip_Arduino_1x15 |  |  |  | 
| P3, P4, P5, P6 | 4 | CONN_01X01 | CONN_01X01 | Socket_Arduino_Nano:1pin_Nano |  |  |  |

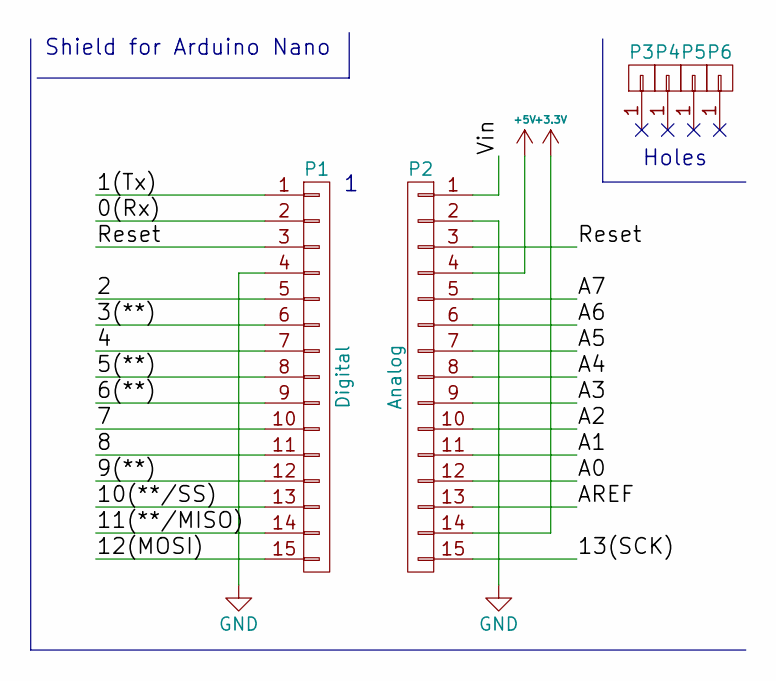
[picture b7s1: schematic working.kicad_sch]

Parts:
P1: Digital; Socket_Strip_Arduino_1x15
P2: Analog; Socket_Strip_Arduino_1x15
P3, P4, P5, P6: CONN_01X01; 1pin_Nano

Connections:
+3V3: P2.14
+5V: P2.4
/0(Rx): P1.2
/1(Tx): P1.1
/2: P1.5
/3(**): P1.6
/4: P1.7
/5(**): P1.8
/6(**): P1.9
/7: P1.10
/8: P1.11
/9(**): P1.12
/10(**/SS): P1.13
/11(**/MISO): P1.14
/12(MOSI): P1.15
/13(SCK): P2.15
/A0: P2.12
/A1: P2.11
/A2: P2.10
/A3: P2.9
/A4: P2.8
/A5: P2.7
/A6: P2.6
/A7: P2.5
/AREF: P2.13
/Reset: P1.3, P2.3
/Vin: P2.1
GND: P1.4, P2.2

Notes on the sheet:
Holes
Shield for Arduino Nano

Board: 2 copper layers, 6 parts (0 on the bottom side), 2 nets, no tracks yet.

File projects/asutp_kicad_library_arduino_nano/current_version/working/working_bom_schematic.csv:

"Source:","C:\gh\oomlout_oomp_project_bot_v_2\projects\asutp_kicad_library_arduino_nano\current_version\working\working.kicad_sch"
"Date:","26/09/2023 17:52:28"
"Tool:","Eeschema 7.0.6"
"Generator:","C:/Program Files/KiCad/7.0/bin/scripting/plugins/bom_csv_grouped_by_value_with_fp.py"
"Component Count:","6"
"Ref","Qnty","Value","Cmp name","Footprint","Description","Vendor","DNP"
"P1","1","Digital","CONN_01X15","Socket_Arduino_Nano:Socket_Strip_Arduino_1x15","","",""
"P2","1","Analog","CONN_01X15","Socket_Arduino_Nano:Socket_Strip_Arduino_1x15","","",""
"P3, P4, P5, P6","4","CONN_01X01","CONN_01X01","Socket_Arduino_Nano:1pin_Nano","","",""

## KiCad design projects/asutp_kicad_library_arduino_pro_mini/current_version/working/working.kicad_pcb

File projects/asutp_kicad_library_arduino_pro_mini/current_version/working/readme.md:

# kicad_library
 
## summary 
* id: asutp_kicad_library_arduino_pro_mini
* user: asutp
* name: kicad_library
* board: arduino_pro_mini
* repo: https://github.com/asutp/kicad-library
* src_file_repo_kicad_pcb: template/Arduino_Pro_Mini/Arduino_Pro_Mini.kicad_pcb
* src_file_repo_kicad_pcb_link: https://github.com/asutp/kicad-library/tree/master/template/Arduino_Pro_Mini/Arduino_Pro_Mini.kicad_pcb

* src_file_repo_sch: template/Arduino_Pro_Mini/Arduino_Pro_Mini.sch
* src_file_repo_sch_link: https://github.com/asutp/kicad-library/tree/master/template/Arduino_Pro_Mini/Arduino_Pro_Mini.sch
* full details link: https://github.com/oomlout/oomlout_oomp_project_bot_v_2/tree/main/projects/asutp_kicad_library_arduino_pro_mini/current_version/working  

## schematic  
  
[schematic (pdf)](working_schematic.pdf) 

## pcb  

[board (pdf)](working.pdf)  

## working_bom
| Id | Designator | Footprint | Quantity | Designation | Supplier and ref |  | None | 
| --- | --- | --- | --- | --- | --- | --- | --- | 
| 1 | P1 | Socket_Strip_Arduino_1x12 | 1 | Digital |  |  | [''] | 
| 2 | P2 | Socket_Strip_Arduino_1x06 | 1 | COM |  |  | [''] | 
| 3 | P3,P5 | Socket_Strip_Arduino_1x02 | 2 | ADC |  |  | [''] | 
| 4 | P4 | Socket_Strip_Arduino_1x12 | 1 | Analog |  |  | [''] | 

## bom_schematic
| Ref | Qnty | Value | Cmp name | Footprint | Description | Vendor | DNP | 
| --- | --- | --- | --- | --- | --- | --- | --- | 
| P1 | 1 | Digital | CONN_01X12 | Socket_Arduino_Pro_Mini:Socket_Strip_Arduino_1x12 |  |  |  | 
| P2 | 1 | COM | CONN_01X06 | Socket_Arduino_Pro_Mini:Socket_Strip_Arduino_1x06 |  |  |  | 
| P3, P5 | 2 | ADC | CONN_01X02 | Socket_Arduino_Pro_Mini:Socket_Strip_Arduino_1x02 |  |  |  | 
| P4 | 1 | Analog | CONN_01X12 | Socket_Arduino_Pro_Mini:Socket_Strip_Arduino_1x12 |  |  |  |

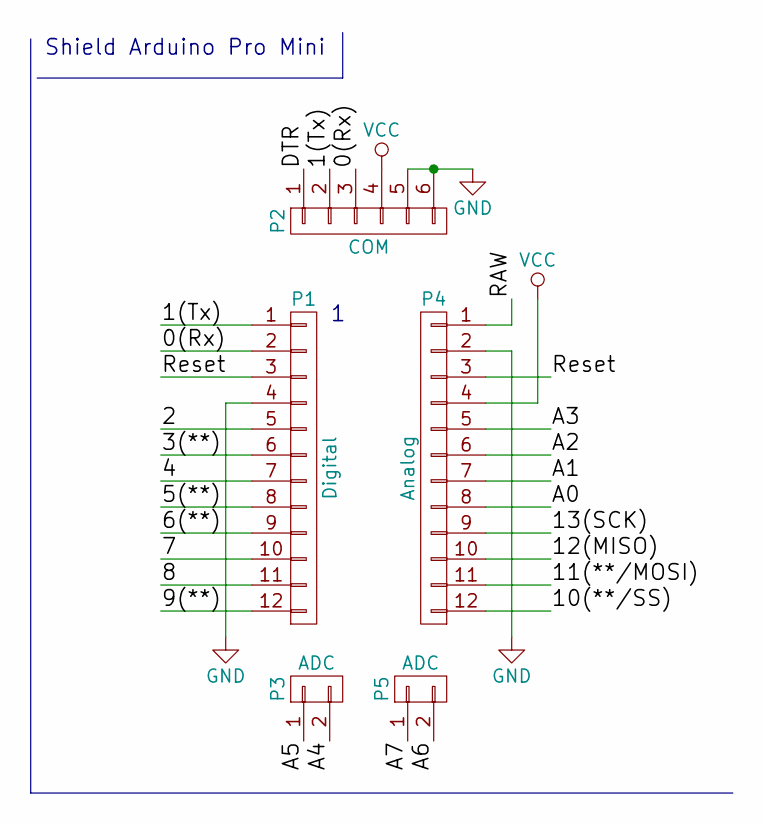
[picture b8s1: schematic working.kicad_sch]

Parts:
P1: Digital; Socket_Strip_Arduino_1x12
P2: COM; Socket_Strip_Arduino_1x06
P3, P5: ADC; Socket_Strip_Arduino_1x02
P4: Analog; Socket_Strip_Arduino_1x12

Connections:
/0(Rx): P1.2, P2.3
/1(Tx): P1.1, P2.2
/2: P1.5
/3(**): P1.6
/4: P1.7
/5(**): P1.8
/6(**): P1.9
/7: P1.10
/8: P1.11
/9(**): P1.12
/10(**/SS): P4.12
/11(**/MOSI): P4.11
/12(MISO): P4.10
/13(SCK): P4.9
/A0: P4.8
/A1: P4.7
/A2: P4.6
/A3: P4.5
/A4: P3.2
/A5: P3.1
/A6: P5.2
/A7: P5.1
/DTR: P2.1
/RAW: P4.1
/Reset: P1.3, P4.3
GND: P1.4, P2.5, P2.6, P4.2
VCC: P2.4, P4.4

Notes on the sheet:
Shield Arduino Pro Mini

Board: 2 copper layers, 5 parts (0 on the bottom side), 5 nets, no tracks yet.
